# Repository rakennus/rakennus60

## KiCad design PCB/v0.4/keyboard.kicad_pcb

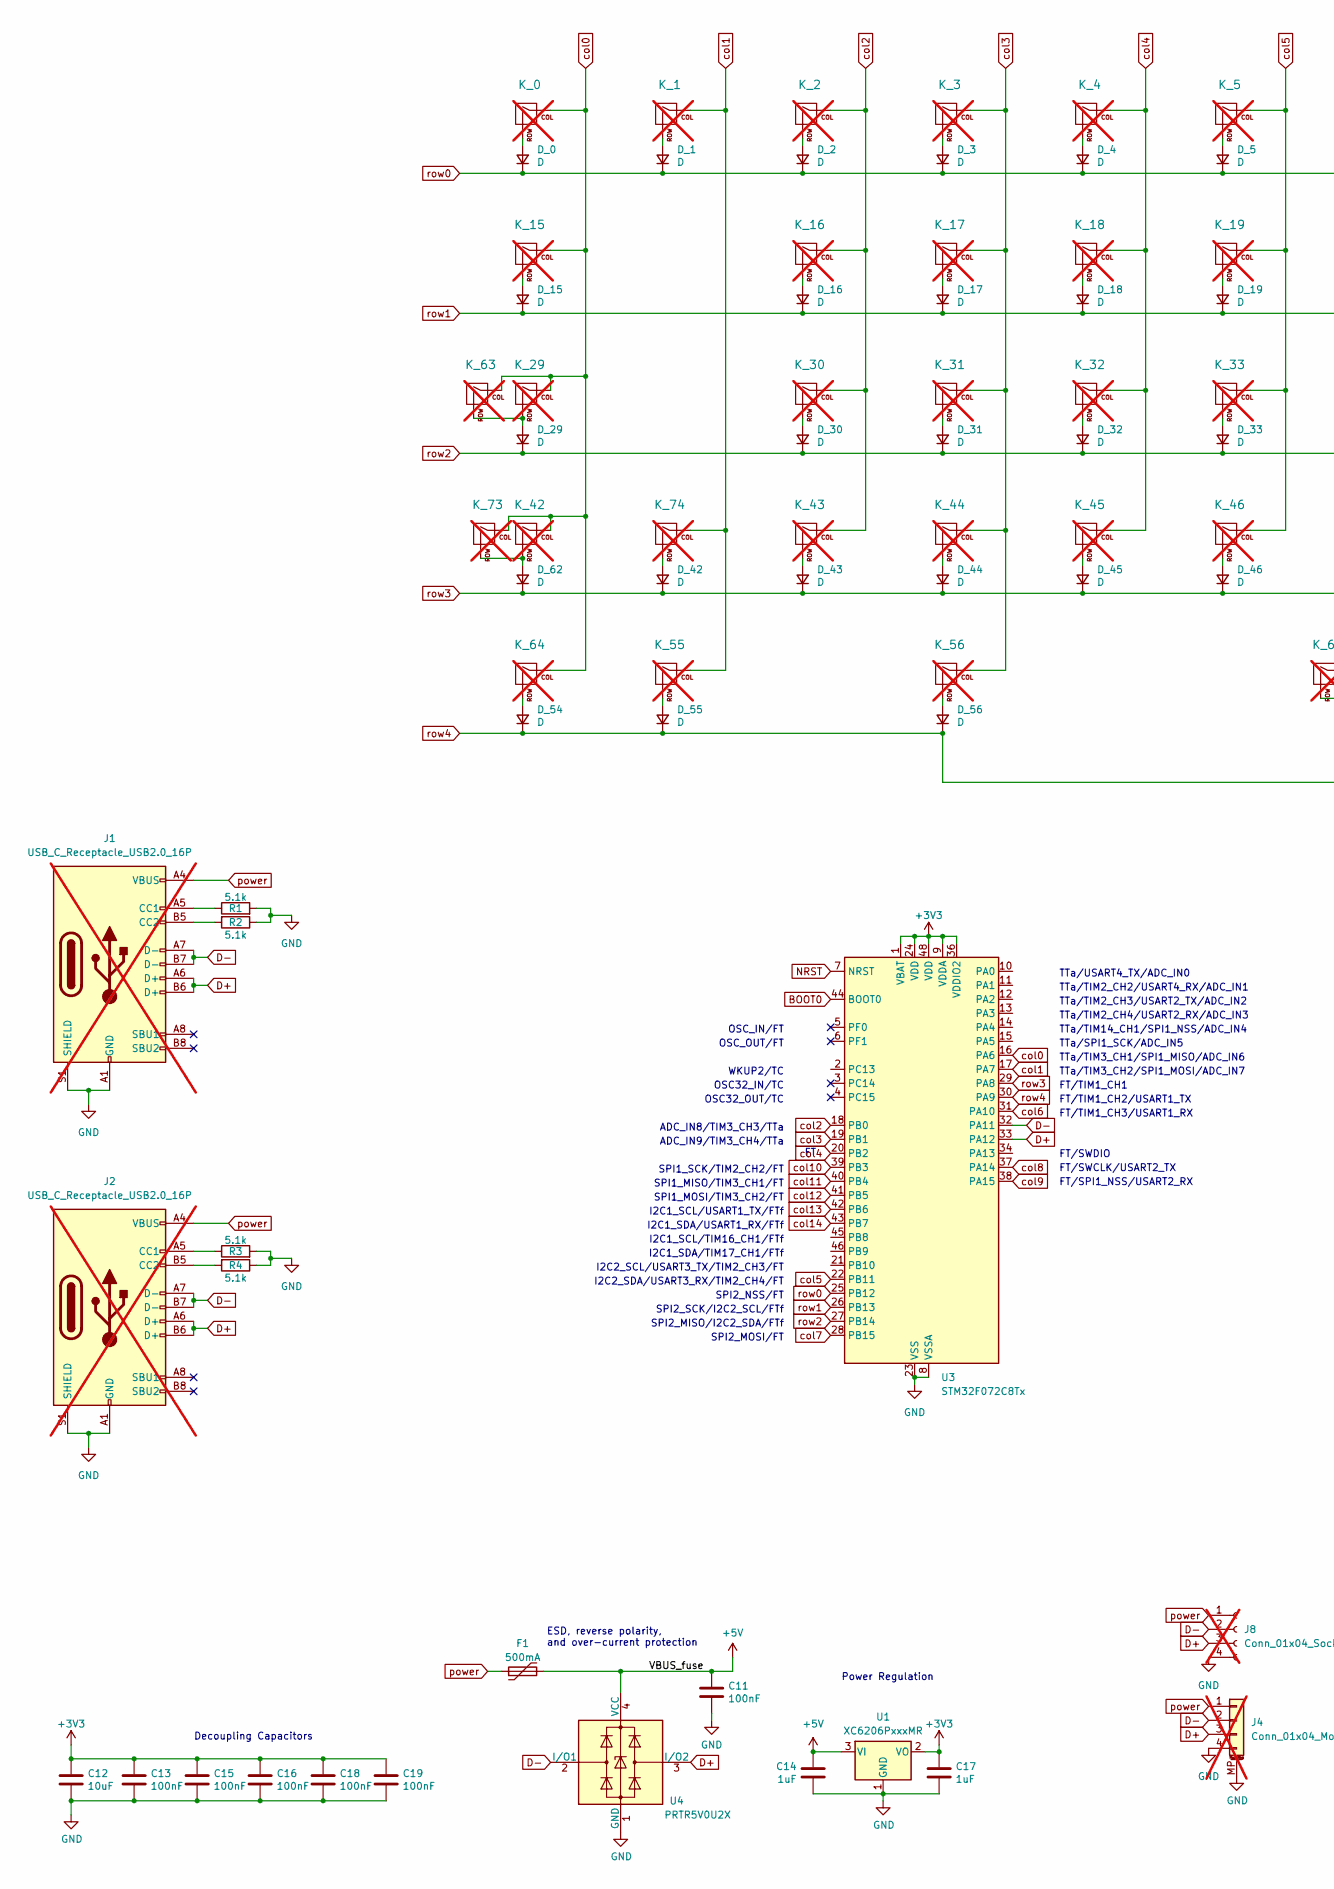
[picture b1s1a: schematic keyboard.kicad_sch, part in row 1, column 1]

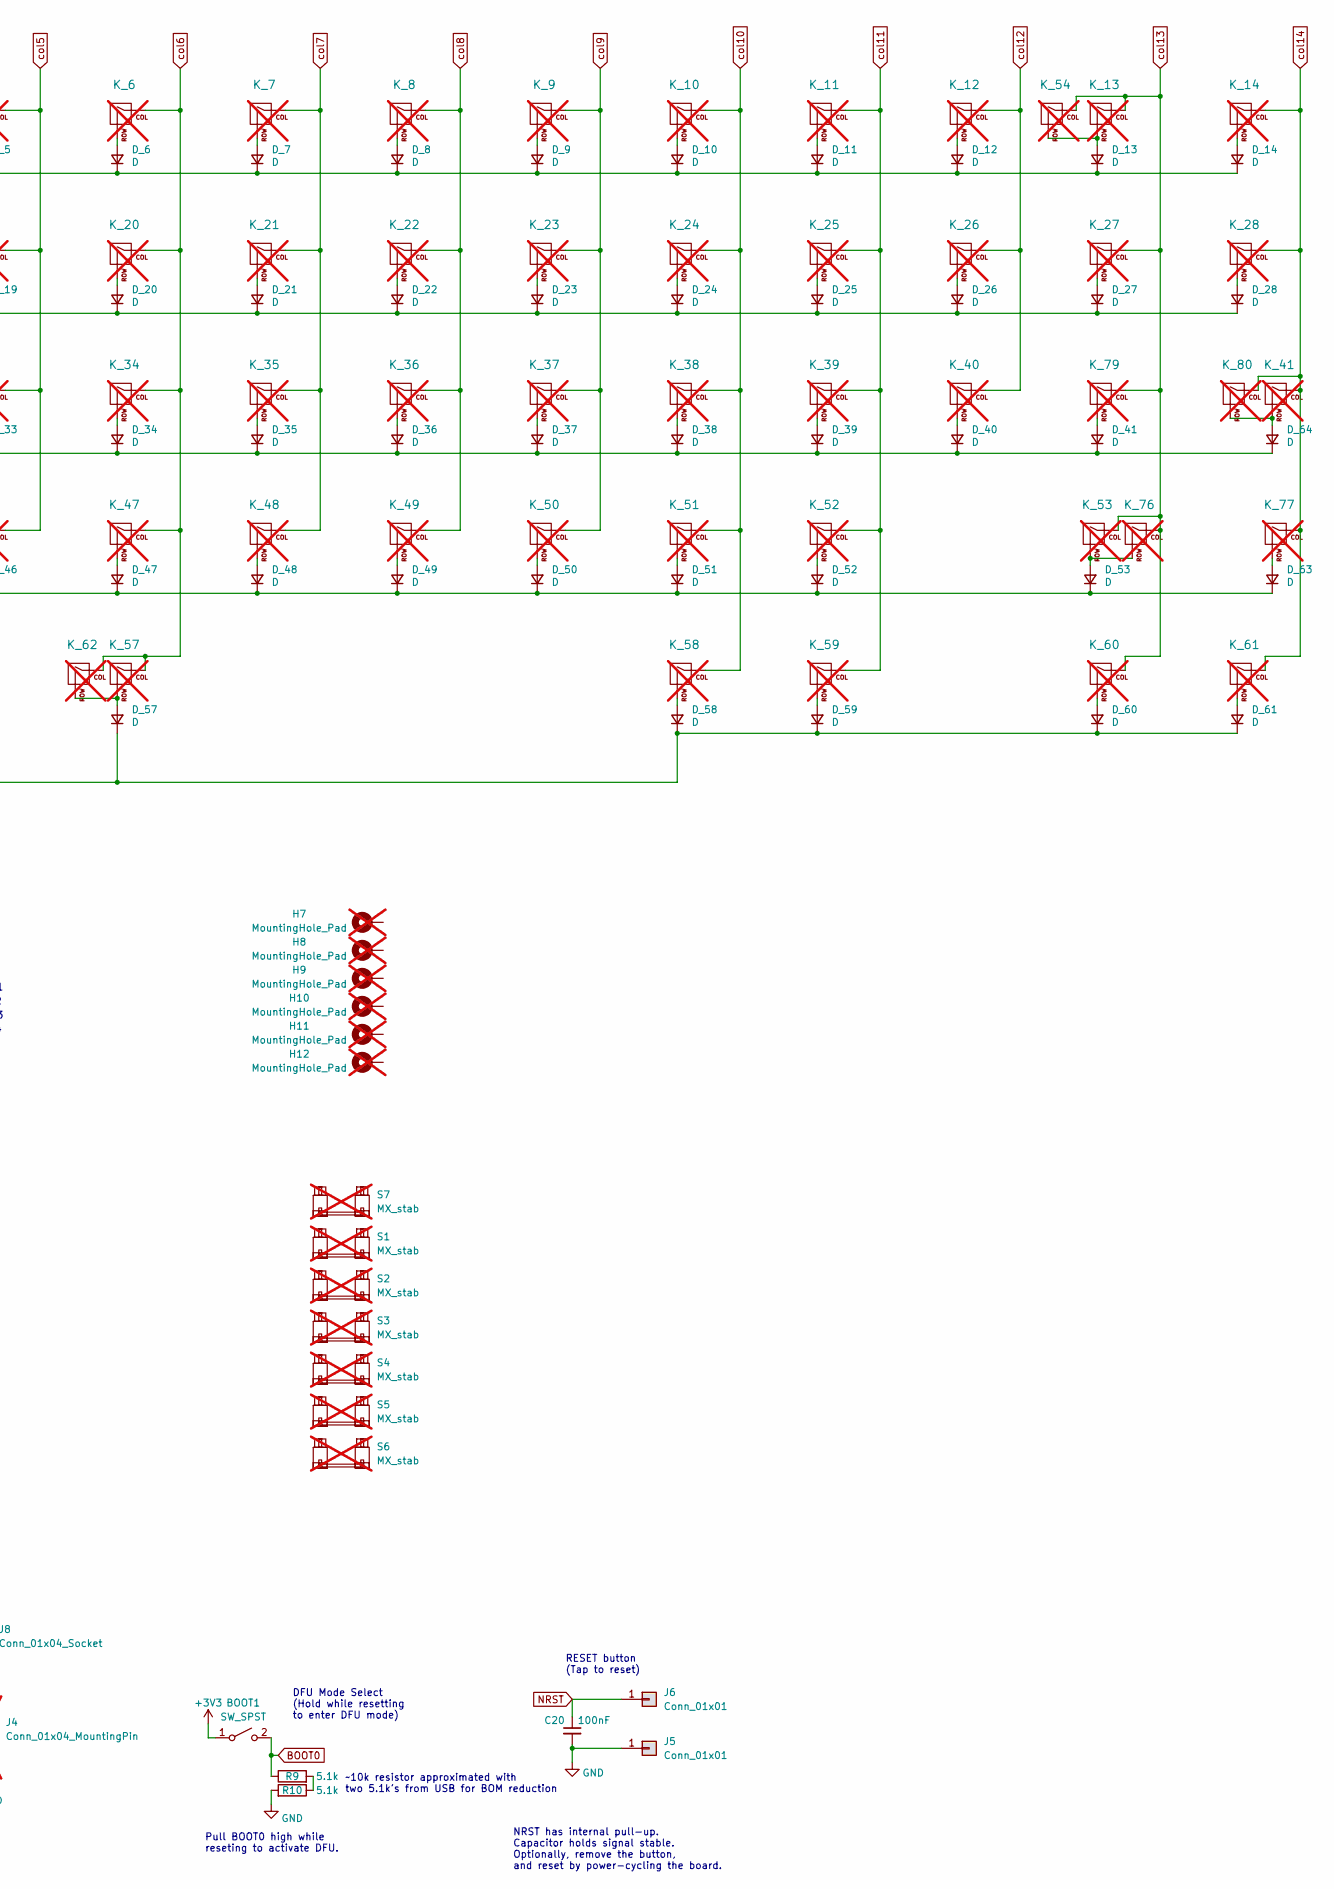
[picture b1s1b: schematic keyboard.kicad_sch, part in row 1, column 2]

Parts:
BOOT1: SW_SPST; SW_SPST_TL3342
C11, C13, C15, C16, C18, C19, C20: 100nF; C_0402_1005Metric; LCSC C307331
C12: 10uF; C_0603_1608Metric; LCSC C307331
C14, C17: 1uF; C_0402_1005Metric; LCSC C307331
D_0, D_1, D_2, D_3, D_4, D_5, D_6, D_7, D_8, D_9, D_10, D_11, D_12, D_13, D_14, D_15, D_16, D_17, D_18, D_19, D_20, D_21, D_22, D_23, D_24, D_25, D_26, D_27, D_28, D_29, D_30, D_31, D_32, D_33, D_34, D_35, D_36, D_37, D_38, D_39, D_40, D_41, D_42, D_43, D_44, D_45, D_46, D_47, D_48, D_49, D_50, D_51, D_52, D_53, D_54, D_55, D_56, D_57, D_58, D_59, D_60, D_61, D_62, D_63, D_64: D; D_SOD-123_vertical
F1: 500mA; Fuse_1206_3216Metric; LCSC C135341
H7, H8: MountingHole_Pad; MountingHole_7mmx2.5mm_M2_Pad; not fitted
H9: MountingHole_Pad; MountingHole_7mm_2.5mm_M2_Pad; not fitted
H10, H11: MountingHole_Pad; MountingHole_5mmx2.5mm_M2_Pad; not fitted
H12: MountingHole_Pad; MountingHole_2.5mm_M2_Pad; not fitted
J1, J2: USB_C_Receptacle_USB2.0_16P; USB_C_Receptacle_G-Switch_GT-USB-7010ASV_custom; not fitted
J4: Conn_01x04_MountingPin; Molex_Pico-EZmate_78171-0004_1x04-1MP_P1.20mm_Vertical; not fitted
J5, J6: Conn_01x01; TestPoint_Pad_3.0x3.0mm
J8: Conn_01x04_Socket; PinHeader_1x04_P2.54mm_Vertical; not fitted
K_0, K_1, K_2, K_3, K_4, K_5, K_6, K_7, K_8, K_9, K_10, K_11, K_12, K_13, K_14, K_16, K_17, K_18, K_19, K_20, K_21, K_22, K_23, K_24, K_25, K_26, K_27, K_30, K_31, K_32, K_33, K_34, K_35, K_36, K_37, K_38, K_39, K_40, K_43, K_44, K_45, K_46, K_47, K_48, K_49, K_50, K_51, K_52, K_74, K_77, K_79: KEYSW; SW_Cherry_MX_PCB_1.00u; not fitted
K_15, K_28: KEYSW; SW_Cherry_MX_PCB_1.50u; not fitted
K_29, K_76: KEYSW; SW_Cherry_MX_PCB_1.75u; not fitted
K_41, K_42: KEYSW; SW_Cherry_MX_PCB_2.25u; not fitted
K_53: KEYSW; SW_Cherry_MX_PCB_2.75u; not fitted
K_54: KEYSW; SW_Cherry_MX_PCB_2.00u; not fitted
K_55: KEYSW; SW_Cherry_MX_PCB_1.00u_x_1.25u; not fitted
K_56, K_64: KEYSW; SW_Cherry_MX_PCB_1.25u_x_1.50u; not fitted
K_57: KEYSW; SW_Cherry_MX_PCB_6.25u; not fitted
K_58, K_63, K_73: KEYSW; SW_Cherry_MX_PCB_1.25u; not fitted
K_59, K_61: KEYSW; SW_Cherry_MX_PCB_1.50u_x_1.25u; not fitted
K_60: KEYSW; SW_Cherry_MX_PCB_1.25u_x_1.00u; not fitted
K_62: KEYSW; SW_Cherry_MX_PCB_7.00u; not fitted
K_80: KEYSW; SW_Cherry_MX_PCB_ISOEnter; not fitted
R1, R2, R3, R4, R9, R10: 5.1k; R_0603_1608Metric_Pad0.98x0.95mm_HandSolder
S1, S2, S3, S6, S7: MX_stab; Stabilizer_Cherry_MX_2.00u; not fitted
S4: MX_stab; Stabilizer_Cherry_MX_6.25u; not fitted
S5: MX_stab; Stabilizer_Cherry_MX_7.00u; not fitted
U1: XC6206PxxxMR; SOT-23-3
U3: STM32F072C8Tx; LQFP-48_7x7mm_P0.5mm
U4: PRTR5V0U2X; SOT-143; LCSC C2827688

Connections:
+3V3: BOOT1.1 (A), C12.1, C13.1, C15.1, C16.1, C17.1, C18.1, C19.1, U1.2 (VO), U3.1 (VBAT), U3.9 (VDDA), U3.24 (VDD), U3.36 (VDDIO2), U3.48 (VDD)
+5V: C11.1, C14.1, F1.2, U1.3 (VI), U4.4 (VCC)
BOOT0: BOOT1.2 (B), R9.1, U3.44 (BOOT0)
D+: J1.A6 (D+), J1.B6 (D+), J2.A6 (D+), J2.B6 (D+), J4.3, J8.3, U3.33 (PA12), U4.3 (I/O2)
D-: J1.A7 (D-), J1.B7 (D-), J2.A7 (D-), J2.B7 (D-), J4.2, J8.2, U3.32 (PA11), U4.2 (I/O1)
GND: C11.2, C12.2, C13.2, C14.2, C15.2, C16.2, C17.2, C18.2, C19.2, C20.2, J1.A1 (GND), J1.A12 (GND), J1.B1 (GND), J1.B12 (GND), J1.S1 (SHIELD), J2.A1 (GND), J2.A12 (GND), J2.B1 (GND), J2.B12 (GND), J2.S1 (SHIELD), J4.4, J4.MP (MountPin), J5.1, J8.4, R1.2, R2.1, R3.2, R4.1, R10.2, U1.1 (GND), U3.8 (VSSA), U3.23 (VSS), U3.35 (VSS), U3.47 (VSS), U4.1 (GND)
NRST: C20.1, J6.1, U3.7 (NRST)
unnamed: D_0.2 (A), K_0.2 (ROW)
unnamed: D_1.2 (A), K_1.2 (ROW)
unnamed: D_2.2 (A), K_2.2 (ROW)
unnamed: D_3.2 (A), K_3.2 (ROW)
unnamed: D_4.2 (A), K_4.2 (ROW)
unnamed: D_5.2 (A), K_5.2 (ROW)
unnamed: D_6.2 (A), K_6.2 (ROW)
unnamed: D_7.2 (A), K_7.2 (ROW)
unnamed: D_8.2 (A), K_8.2 (ROW)
unnamed: D_9.2 (A), K_9.2 (ROW)
unnamed: D_10.2 (A), K_10.2 (ROW)
unnamed: D_11.2 (A), K_11.2 (ROW)
unnamed: D_12.2 (A), K_12.2 (ROW)
unnamed: D_13.2 (A), K_13.2 (ROW), K_54.2 (ROW)
unnamed: D_14.2 (A), K_14.2 (ROW)
unnamed: D_15.2 (A), K_15.2 (ROW)
unnamed: D_16.2 (A), K_16.2 (ROW)
unnamed: D_17.2 (A), K_17.2 (ROW)
unnamed: D_18.2 (A), K_18.2 (ROW)
unnamed: D_19.2 (A), K_19.2 (ROW)
unnamed: D_20.2 (A), K_20.2 (ROW)
unnamed: D_21.2 (A), K_21.2 (ROW)
unnamed: D_22.2 (A), K_22.2 (ROW)
unnamed: D_23.2 (A), K_23.2 (ROW)
unnamed: D_24.2 (A), K_24.2 (ROW)
unnamed: D_25.2 (A), K_25.2 (ROW)
unnamed: D_26.2 (A), K_26.2 (ROW)
unnamed: D_27.2 (A), K_27.2 (ROW)
unnamed: D_28.2 (A), K_28.2 (ROW)
unnamed: D_29.2 (A), K_29.2 (ROW), K_63.2 (ROW)
unnamed: D_30.2 (A), K_30.2 (ROW)
unnamed: D_31.2 (A), K_31.2 (ROW)
unnamed: D_32.2 (A), K_32.2 (ROW)
unnamed: D_33.2 (A), K_33.2 (ROW)
unnamed: D_34.2 (A), K_34.2 (ROW)
unnamed: D_35.2 (A), K_35.2 (ROW)
unnamed: D_36.2 (A), K_36.2 (ROW)
unnamed: D_37.2 (A), K_37.2 (ROW)
unnamed: D_38.2 (A), K_38.2 (ROW)
unnamed: D_39.2 (A), K_39.2 (ROW)
unnamed: D_40.2 (A), K_40.2 (ROW)
unnamed: D_41.2 (A), K_79.2 (ROW)
unnamed: D_42.2 (A), K_74.2 (ROW)
unnamed: D_43.2 (A), K_43.2 (ROW)
unnamed: D_44.2 (A), K_44.2 (ROW)
unnamed: D_45.2 (A), K_45.2 (ROW)
unnamed: D_46.2 (A), K_46.2 (ROW)
unnamed: D_47.2 (A), K_47.2 (ROW)
unnamed: D_48.2 (A), K_48.2 (ROW)
unnamed: D_49.2 (A), K_49.2 (ROW)
unnamed: D_50.2 (A), K_50.2 (ROW)
unnamed: D_51.2 (A), K_51.2 (ROW)
unnamed: D_52.2 (A), K_52.2 (ROW)
unnamed: D_53.2 (A), K_53.2 (ROW), K_76.2 (ROW)
unnamed: D_54.2 (A), K_64.2 (ROW)
unnamed: D_55.2 (A), K_55.2 (ROW)
unnamed: D_56.2 (A), K_56.2 (ROW)
unnamed: D_57.2 (A), K_57.2 (ROW), K_62.2 (ROW)
unnamed: D_58.2 (A), K_58.2 (ROW)
unnamed: D_59.2 (A), K_59.2 (ROW)
unnamed: D_60.2 (A), K_60.2 (ROW)
unnamed: D_61.2 (A), K_61.2 (ROW)
unnamed: D_62.2 (A), K_42.2 (ROW), K_73.2 (ROW)
unnamed: D_63.2 (A), K_77.2 (ROW)
unnamed: D_64.2 (A), K_41.2 (ROW), K_80.2 (ROW)
unnamed: J1.A5 (CC1), R1.1
unnamed: J1.B5 (CC2), R2.2
unnamed: J2.A5 (CC1), R3.1
unnamed: J2.B5 (CC2), R4.2
unnamed: R9.2, R10.1
col0: K_0.1 (COL), K_15.1 (COL), K_29.1 (COL), K_42.1 (COL), K_63.1 (COL), K_64.1 (COL), K_73.1 (COL), U3.16 (PA6)
col1: K_1.1 (COL), K_55.1 (COL), K_74.1 (COL), U3.17 (PA7)
col2: K_2.1 (COL), K_16.1 (COL), K_30.1 (COL), K_43.1 (COL), U3.18 (PB0)
col3: K_3.1 (COL), K_17.1 (COL), K_31.1 (COL), K_44.1 (COL), K_56.1 (COL), U3.19 (PB1)
col4: K_4.1 (COL), K_18.1 (COL), K_32.1 (COL), K_45.1 (COL), U3.20 (PB2)
col5: K_5.1 (COL), K_19.1 (COL), K_33.1 (COL), K_46.1 (COL), U3.22 (PB11)
col6: K_6.1 (COL), K_20.1 (COL), K_34.1 (COL), K_47.1 (COL), K_57.1 (COL), K_62.1 (COL), U3.31 (PA10)
col7: K_7.1 (COL), K_21.1 (COL), K_35.1 (COL), K_48.1 (COL), U3.28 (PB15)
col8: K_8.1 (COL), K_22.1 (COL), K_36.1 (COL), K_49.1 (COL), U3.37 (PA14)
col9: K_9.1 (COL), K_23.1 (COL), K_37.1 (COL), K_50.1 (COL), U3.38 (PA15)
col10: K_10.1 (COL), K_24.1 (COL), K_38.1 (COL), K_51.1 (COL), K_58.1 (COL), U3.39 (PB3)
col11: K_11.1 (COL), K_25.1 (COL), K_39.1 (COL), K_52.1 (COL), K_59.1 (COL), U3.40 (PB4)
col12: K_12.1 (COL), K_26.1 (COL), K_40.1 (COL), U3.41 (PB5)
col13: K_13.1 (COL), K_27.1 (COL), K_53.1 (COL), K_54.1 (COL), K_60.1 (COL), K_76.1 (COL), K_79.1 (COL), U3.42 (PB6)
col14: K_14.1 (COL), K_28.1 (COL), K_41.1 (COL), K_61.1 (COL), K_77.1 (COL), K_80.1 (COL), U3.43 (PB7)
power: F1.1, J1.A4 (VBUS), J1.A9 (VBUS), J1.B4 (VBUS), J1.B9 (VBUS), J2.A4 (VBUS), J2.A9 (VBUS), J2.B4 (VBUS), J2.B9 (VBUS), J4.1, J8.1
row0: D_0.1 (K), D_1.1 (K), D_2.1 (K), D_3.1 (K), D_4.1 (K), D_5.1 (K), D_6.1 (K), D_7.1 (K), D_8.1 (K), D_9.1 (K), D_10.1 (K), D_11.1 (K), D_12.1 (K), D_13.1 (K), D_14.1 (K), U3.25 (PB12)
row1: D_15.1 (K), D_16.1 (K), D_17.1 (K), D_18.1 (K), D_19.1 (K), D_20.1 (K), D_21.1 (K), D_22.1 (K), D_23.1 (K), D_24.1 (K), D_25.1 (K), D_26.1 (K), D_27.1 (K), D_28.1 (K), U3.26 (PB13)
row2: D_29.1 (K), D_30.1 (K), D_31.1 (K), D_32.1 (K), D_33.1 (K), D_34.1 (K), D_35.1 (K), D_36.1 (K), D_37.1 (K), D_38.1 (K), D_39.1 (K), D_40.1 (K), D_41.1 (K), D_64.1 (K), U3.27 (PB14)
row3: D_42.1 (K), D_43.1 (K), D_44.1 (K), D_45.1 (K), D_46.1 (K), D_47.1 (K), D_48.1 (K), D_49.1 (K), D_50.1 (K), D_51.1 (K), D_52.1 (K), D_53.1 (K), D_62.1 (K), D_63.1 (K), U3.29 (PA8)
row4: D_54.1 (K), D_55.1 (K), D_56.1 (K), D_57.1 (K), D_58.1 (K), D_59.1 (K), D_60.1 (K), D_61.1 (K), U3.30 (PA9)

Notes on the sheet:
FT/SWDIO
FT/TIM1_CH3/USART1_RX
TTa/TIM14_CH1/SPI1_NSS/ADC_IN4
FT/SWCLK/USART2_TX
TTa/USART4_TX/ADC_IN0
I2C1_SCL/USART1_TX/FTf
SPI2_MISO/I2C2_SDA/FTf
I2C1_SDA/TIM17_CH1/FTf
SPI2_SCK/I2C2_SCL/FTf
OSC32_IN/TC
TTa/SPI1_SCK/ADC_IN5
TTa/TIM2_CH2/USART4_RX/ADC_IN1
SPI1_SCK/TIM2_CH2/FT
I2C2_SCL/USART3_TX/TIM2_CH3/FT
I2C1_SDA/USART1_RX/FTf
WKUP2/TC
OSC_IN/FT
DFU Mode Select (Hold while resetting to enter DFU mode)
Power Regulation
TTa/TIM3_CH1/SPI1_MISO/ADC_IN6
SPI1_MISO/TIM3_CH1/FT
ADC_IN9/TIM3_CH4/TTa
FT/SPI1_NSS/USART2_RX
FT/TIM1_CH2/USART1_TX
I2C2_SDA/USART3_RX/TIM2_CH4/FT
SPI2_NSS/FT
Pull BOOT0 high while reseting to activate DFU.
RESET button (Tap to reset)
TTa/TIM3_CH2/SPI1_MOSI/ADC_IN7
SPI2_MOSI/FT
OSC_OUT/FT
I2C1_SCL/TIM16_CH1/FTf
TTa/TIM2_CH4/USART2_RX/ADC_IN3
NRST has internal pull-up. Capacitor holds signal stable. Optionally, remove the button, and reset by power-cycling the board.
ESD, reverse polarity, and over-current protection
SPI1_MOSI/TIM3_CH2/FT
FT/TIM1_CH1
TTa/TIM2_CH3/USART2_TX/ADC_IN2
Decoupling Capacitors
~10k resistor approximated with two 5.1k's from USB for BOM reduction

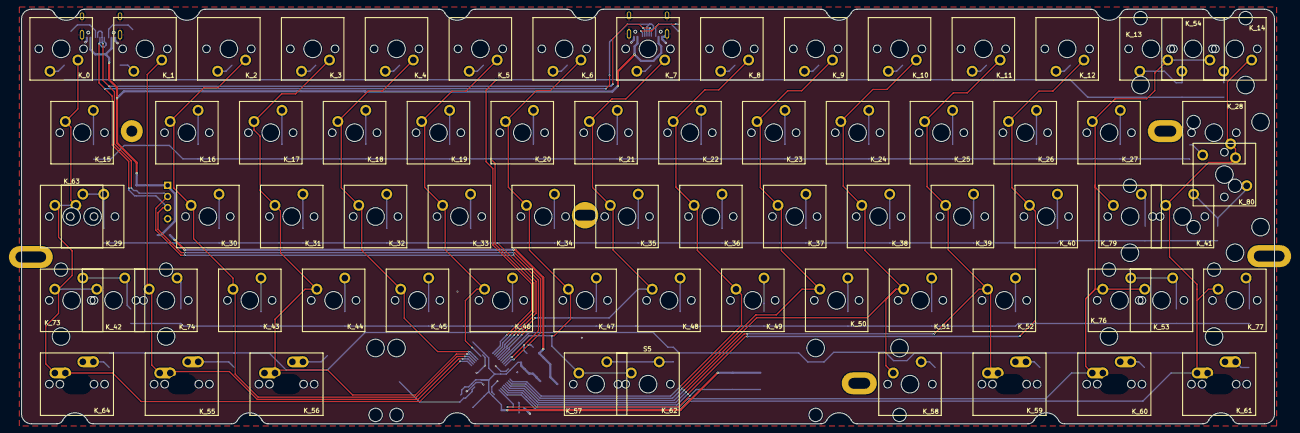
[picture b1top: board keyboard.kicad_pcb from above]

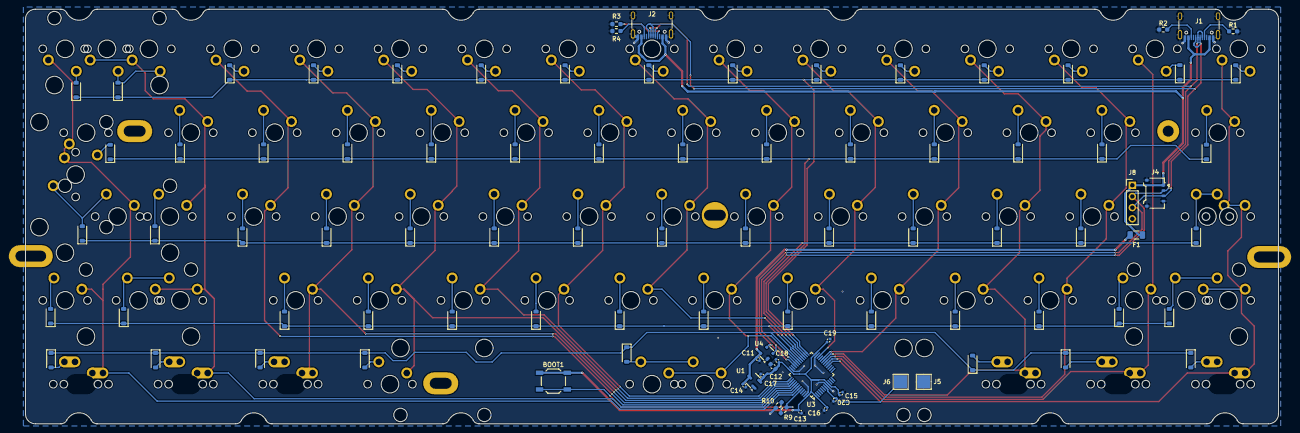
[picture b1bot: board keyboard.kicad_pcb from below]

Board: 2 copper layers, 284.7 x 94.2 mm, 176 parts (98 on the bottom side), 98 nets.

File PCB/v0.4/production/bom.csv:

Designator,Footprint,Quantity,Value,LCSC Part #
BOOT1,SW_SPST_TL3342,1,SW_SPST,
"C11, C13, C15, C16, C18, C19, C20",402,7,100nF,C307331
C12,603,1,10uF,C307331
"C14, C17",402,2,1uF,C307331
"D_0, D_1, D_10, D_11, D_12, D_13, D_14, D_15, D_16, D_17, D_18, D_19, D_2, D_20, D_21, D_22, D_23, D_24, D_25, D_26, D_27, D_28, D_29, D_3, D_30, D_31, D_32, D_33, D_34, D_35, D_36, D_37, D_38, D_39, D_4, D_40, D_41, D_42, D_43, D_44, D_45, D_46, D_47, D_48, D_49, D_5, D_50, D_51, D_52, D_53, D_54, D_55, D_56, D_57, D_58, D_59, D_6, D_60, D_61, D_62, D_63, D_64, D_7, D_8, D_9",D_SOD-123_vertical,65,D,
F1,1206,1,500mA,C135341
"J5, J6",TestPoint_Pad_3.0x3.0mm,2,Conn_01x01,
"R1, R10, R2, R3, R4, R9",603,6,5.1k,
U1,SOT-23-3,1,XC6206PxxxMR,
U3,LQFP-48_7x7mm_P0.5mm,1,STM32F072C8Tx,
U4,SOT-143,1,PRTR5V0U2X,C2827688

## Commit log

2024-08-16 first routing
2024-08-16 new folder structure
2024-08-20 dfasdasfawef
2024-08-21 merged keyboard footprints
2024-08-25 new version
2024-09-13 final version before first production
